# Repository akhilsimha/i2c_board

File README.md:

- The project was mainly started to learn PCB designing using KiCad. 
- The board was designed out of personal interest to practice the I2C mode of communication.

- The Rev 1.0 was ordered from JLC PCB.

Update 18.07.2025:
- The boards arrived from JLC PCB, and they look good:

- I now have to ask my seniors for feedback and suggestions.

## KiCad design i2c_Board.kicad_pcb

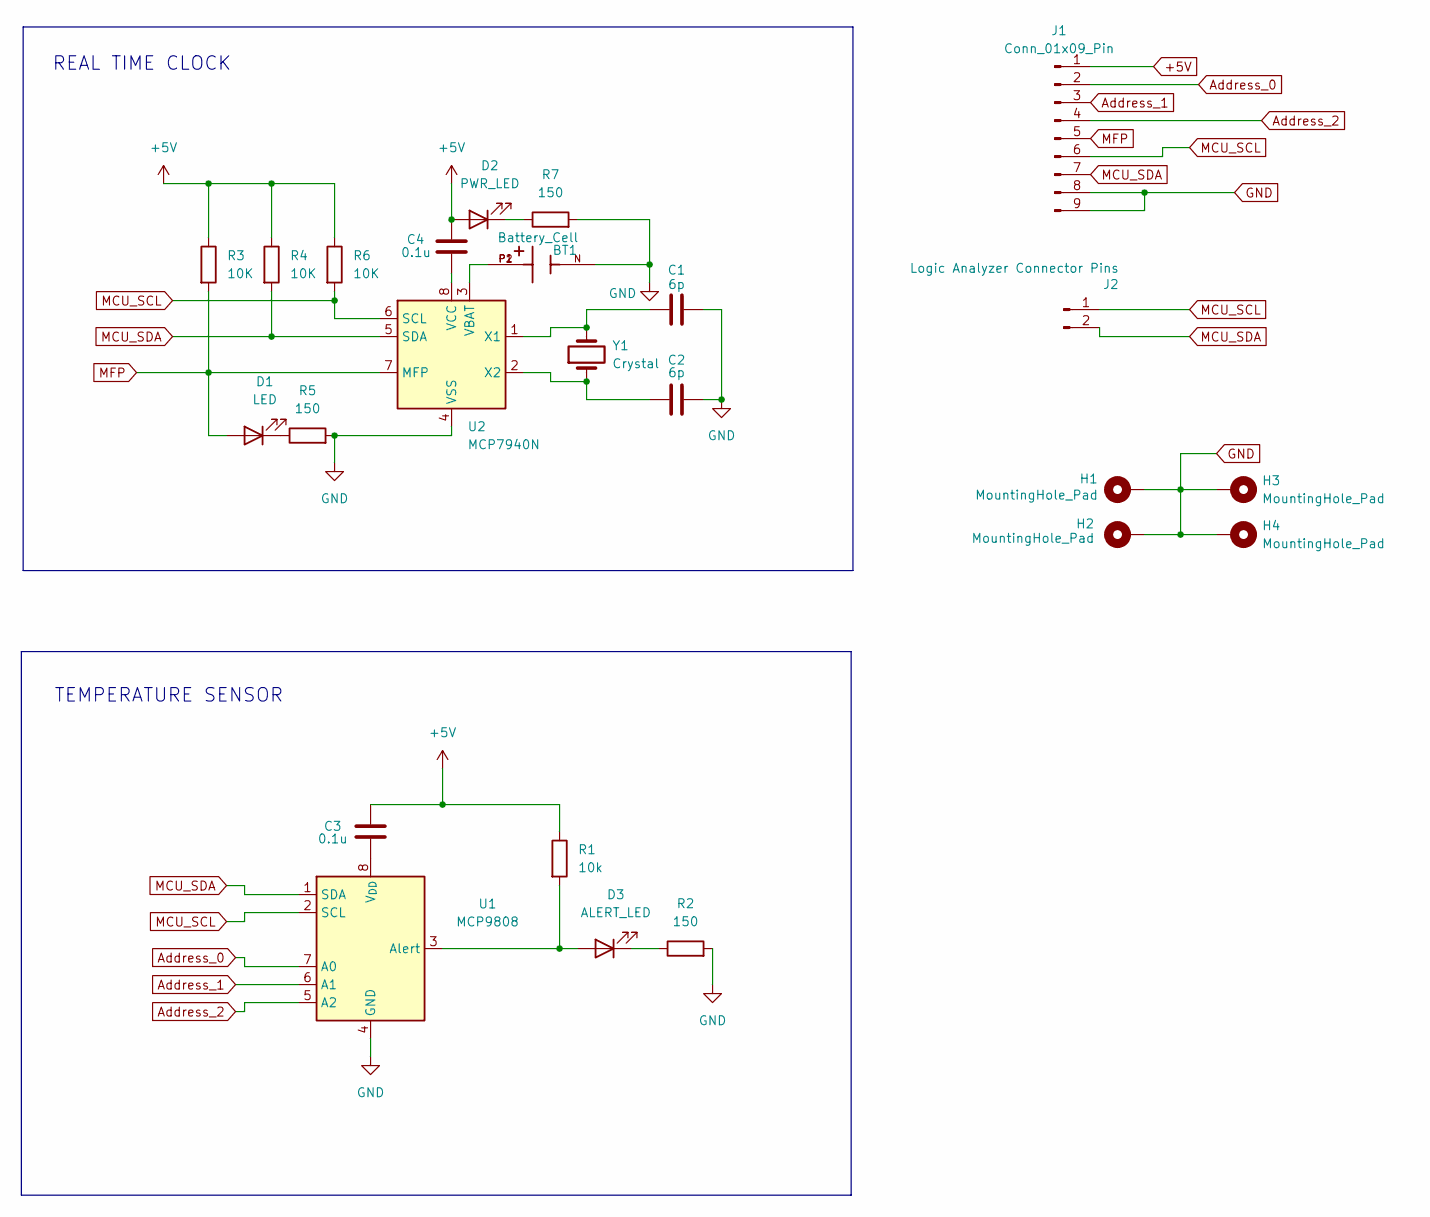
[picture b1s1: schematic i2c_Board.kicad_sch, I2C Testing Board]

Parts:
BT1: Battery_Cell; BAT_BAT-HLD-002-SMT
C1, C2: 6p; C_0805_2012Metric_Pad1.18x1.45mm_HandSolder
C3, C4: 0.1u; C_0805_2012Metric_Pad1.18x1.45mm_HandSolder
D1: LED; LED_0805_2012Metric_Pad1.15x1.40mm_HandSolder
D2: PWR_LED; LED_0805_2012Metric_Pad1.15x1.40mm_HandSolder
D3: ALERT_LED; LED_0805_2012Metric_Pad1.15x1.40mm_HandSolder
H1, H2, H3, H4: MountingHole_Pad; MountingHole_2.2mm_M2_DIN965_Pad
J1: Conn_01x09_Pin; PinHeader_1x09_P2.54mm_Vertical
J2: Logic Analyzer Connector Pins; PinHeader_1x02_P2.54mm_Vertical
R1: 10k; R_0805_2012Metric_Pad1.20x1.40mm_HandSolder
R2, R5, R7: 150; R_0805_2012Metric_Pad1.20x1.40mm_HandSolder
R3, R4, R6: 10K; R_0805_2012Metric_Pad1.20x1.40mm_HandSolder
U1: MCP9808; MSOP-8_3x3mm_P0.65mm
U2: MCP7940N; SOIC127P600X175-8N
Y1: Crystal; XTAL_VMK3-9001-32K7680000TR

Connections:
+5V: C3.1, C4.1, D2.2 (A), J1.1, R1.1, R3.1, R4.1, R6.1
Address_0: J1.2, U1.7 (A0)
Address_1: J1.3, U1.6 (A1)
Address_2: J1.4, U1.5 (A2)
GND: BT1.N, C1.1, C2.1, H1.1, H2.1, H3.1, H4.1, J1.8, J1.9, R2.2, R5.2, R7.2, U1.4 (GND), U2.4 (VSS)
MCU_SCL: J1.6, J2.1, R6.2, U1.2 (SCL), U2.6 (SCL)
MCU_SDA: J1.7, J2.2, R4.2, U1.1 (SDA), U2.5 (SDA)
MFP: D1.2 (A), J1.5, R3.2, U2.7 (MFP)
unnamed: D1.1 (K), R5.1
unnamed: D2.1 (K), R7.1
unnamed: D3.2 (A), R1.2, U1.3 (Alert)
unnamed: D3.1 (K), R2.1
unnamed: C3.2, U1.8 (V_{DD})
unnamed: BT1.P1, BT1.P2, U2.3 (VBAT)
unnamed: C4.2, U2.8 (VCC)
unnamed: C1.2, U2.1 (X1), Y1.2
unnamed: C2.2, U2.2 (X2), Y1.1

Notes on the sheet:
REAL TIME CLOCK
TEMPERATURE SENSOR

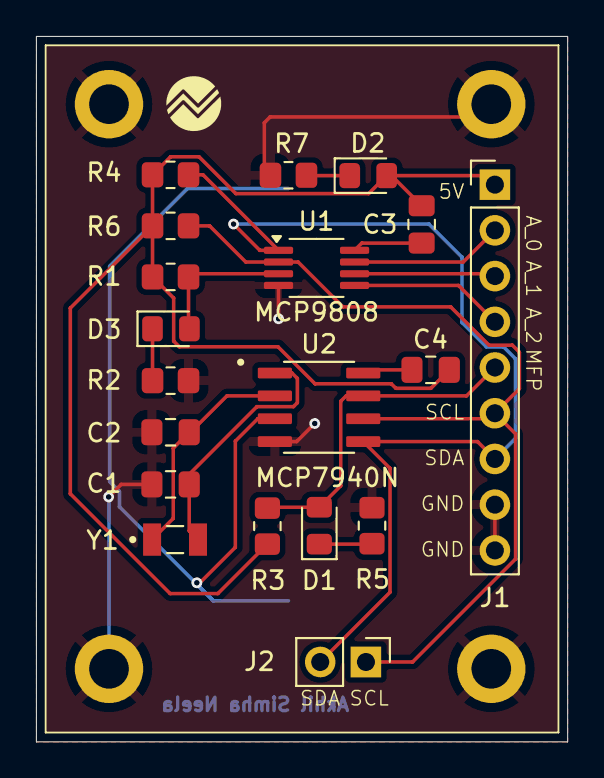
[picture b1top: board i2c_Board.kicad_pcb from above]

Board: 2 copper layers, 29.5 x 39.2 mm, 24 parts (1 on the bottom side), 17 nets.

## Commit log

2025-06-28 Updated footprints
2025-07-10 Updated Gitignore
2025-07-10 Removed Backup Folder
2025-07-10 Remove .bak files from tracking
2025-07-18 Modified footprint & Rearranged routing
2025-07-23 Changed Capacitor value from 6nF to 6pF
2025-07-25 Optimised board to smaller size & Added Ground Plane
2025-07-25 Added Borders
2025-07-29 Moved battery holder position
2025-07-30 Added Decoupling Capacitors
2025-08-02 Flipped incorrect battery polarity
